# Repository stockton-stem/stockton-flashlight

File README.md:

Stockton Flashlight 
===================

License
=======

Flashlight design © 2015 Chris Luke.
Flashlight documentation © 2015 Chris Luke.

This project is licensed with the CERN Open Hardware Licence v1.2.

You may redistribute and modify this project under the terms of the CERN OHL
v.1.2. (http://ohwr.org/cernohl). This project is distributed WITHOUT ANY
EXPRESS OR IMPLIED WARRANTY, INCLUDING OF MERCHANTABILITY, SATISFACTORY
QUALITY AND FITNESS FOR A PARTICULAR PURPOSE. Please see the CERN OHL v.1.2
for applicable Conditions.

Introduction
============

This project is intended to introduce some basic concepts of electronic and
mechanical design. There is a small amount of soldering and a small amount of
assembly. The result of this is a working and powerful flashlight.

The latest version of this documentation and of the Flashlight project is
available at https://github.com/stockton-stem/stockton-flashlight .

The design is not without flaws however, and deliberately so. As you build the
flashlight you should pay attention to the steps and ask yourself how you
might improve it.

Design
======

The project is centered on using a length of 1 inch Schedule 40 PVC pipe which
has the desirable characteristic of its internal diameter being just a little
greater than the diameter of ordinary “C” cell batteries. As part of the
design we settled on using a small printed circuit board at each end of the
tube to hold components, to hold the batteries in place and to make electrical
contact with the batteries.

The primary element of the flashlight is its light source and we have selected
an extremely bright LED (Cree® XLamp® ML-E). Whilst ideally suited for use in
a flashlight, LEDs require some consideration; they must be soldered to a
circuit board, powerful LEDs generate lots of heat and LEDs require some type
of current limited to prevent them from burning out.

To limit the current supplied to the LED we use an inexpensive 350mA current
regulator (ADDtek® AMC7135) that can operate on an input voltage of up to 6V.

Since LEDs tend to have a wide light distribution angle and for a flashlight
we need a more focused beam, we use a curved reflector. The reflectors in this
design are inexpensive plastic devices but are effective enough to provide
very good value.

To hold the LED board and the reflector in place we use a simple 1 inch PVC
coupler machined at one end with a large countersink tool to accept the
reflector. Any such coupler will work but the female NPT coupler gives the
flashlight a particularly rugged look. The positive (+) terminal of the
batteries makes direct contact with the underside of the LED circuit board.

The other end of the flashlight has a copper spring soldered to a circuit
board to make contact with, and push against, the negative (-) terminal of the
batteries. On the opposite side of this board there is a simple pushbutton
toggle switch to turn the flashlight on and off.

To secure this board to the flashlight, and to enable removal to change
batteries, two solder lugs are screwed to the side of the body and their ends
soldered to the board.

To provide an electrical connection between the two boards we use self-
adhesive copper tape which runs along the inside of the PVC tube. It makes
contact with the LED board using plated pads on the underside of the board.
The button board contacts the tape using the solder lugs used to hold the
board in place.

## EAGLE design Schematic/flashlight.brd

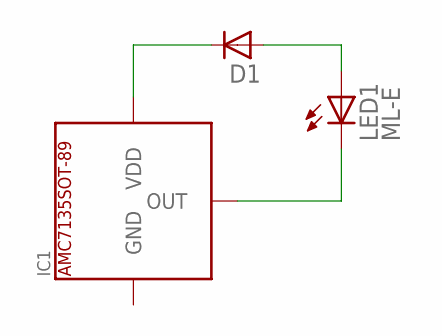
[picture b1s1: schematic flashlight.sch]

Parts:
D1: DIODE-RECTIFIER323; DIODE323
IC1: AMC7135SOT-89; SOT89-R
LED1: ML-E

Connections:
GND: IC1.3 (GND)
unnamed: IC1.2 (OUT), LED1.C@1 (C)
unnamed: D1.C, IC1.1 (VDD)

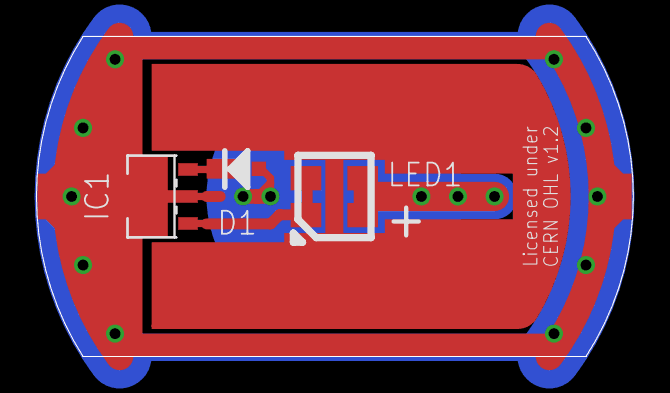
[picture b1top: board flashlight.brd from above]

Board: 2 copper layers, 33.2 x 17.8 mm, 3 parts (0 on the bottom side), 2 nets.

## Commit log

2015-03-29 initial commit, brd rev 1.1
2015-03-29 ignore some stuff
2015-03-29 remove *.pro - they're output files
2015-03-30 version 2 of the top board
2015-03-30 add current regulator datasheet
2015-03-30 add excel tmp file to gitignore
2015-03-30 rev 2.0 of the bottom board, plus minor tweaks to the top board
2015-03-30 update bom with selected parts
2015-03-31 top board rev 3 (with the 350ma reg)
2015-04-02 rev 3 of the bottom
2015-04-08 update bom; add alt regulator
2015-04-08 make unused switch pad act same as middle pad
    this allows switches with just two pins in the same place as the
    outer pads work
2015-04-11 make solder-mask text thicker
2015-04-11 minor bom updates
2015-04-11 expand the solder mask for the LED thermal pad
    should make it easier to hand-solder the thermal pad to the board
2015-04-12 add stockton logo to solder mask
    add thermal mask to top
    replace rhs of top with curved wire
    label pins of switch on bottom
    reduce size of tab solder area
2015-04-13 bom updates - cleanup the bom
    also add some misc items, like plastic bags, batteries
2015-04-15 fix logo on bottom brd
2015-04-19 create docs dir; add the start of some build instructions
2015-04-19 Move the Eagle files into a Schematic directory
2015-04-19 update gitignore
2015-04-19 add brief README, LICENSE, and more doc.
    This project is now CERN OHL licensed.
2015-04-19 add references to the LICENSE in several places
    add a change history file
2015-04-20 fix pin layout of AMC7135 package
2015-04-20 rename datasheet to something more recognizable
2015-04-20 several small changes to improve clarify and flow
2015-04-20 cleanup routing on the board
2015-04-20 add pcb layout to cover page :)
2015-04-20 bunch of tweaks to the doc
2015-04-21 add cover page images, more design info
2015-04-21 add some images of the fl and boards
2015-04-21 extraneous license pdf file
2015-04-22 oodles of doc updates
2015-04-23 tweak copyright notice; add design info to README
2015-04-24 make the (+) terminal footprint a better circle
2015-04-24 Add headers/footer, add PDF, tweak design doc
    Now I need to remember to keep the PDF in sync!
2015-04-26 add lots of pictures to the build blurb!
2015-04-26 small documentation fixes
2015-04-26 annotate the front cover images; small mistakes
2015-04-26 tweaks and typos and stuff
2015-06-25 Start revision 3.3 by adding a protection diode.
    * Add a protection diode for the current regulator.
    * Adjust the footprint of the switch to make it slightly easier
    to position and solder.
    * Add text for the Diode to the documentation; however it should
    have updated pictures for the board throughout since this is
    more than a cosmetic change.
2018-04-15 Update github links
    - The repository was moved into the Stockton STEM org on Github.

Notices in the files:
Schematic/flashlight.brd:
Licensed under
CERN OHL v1.2
